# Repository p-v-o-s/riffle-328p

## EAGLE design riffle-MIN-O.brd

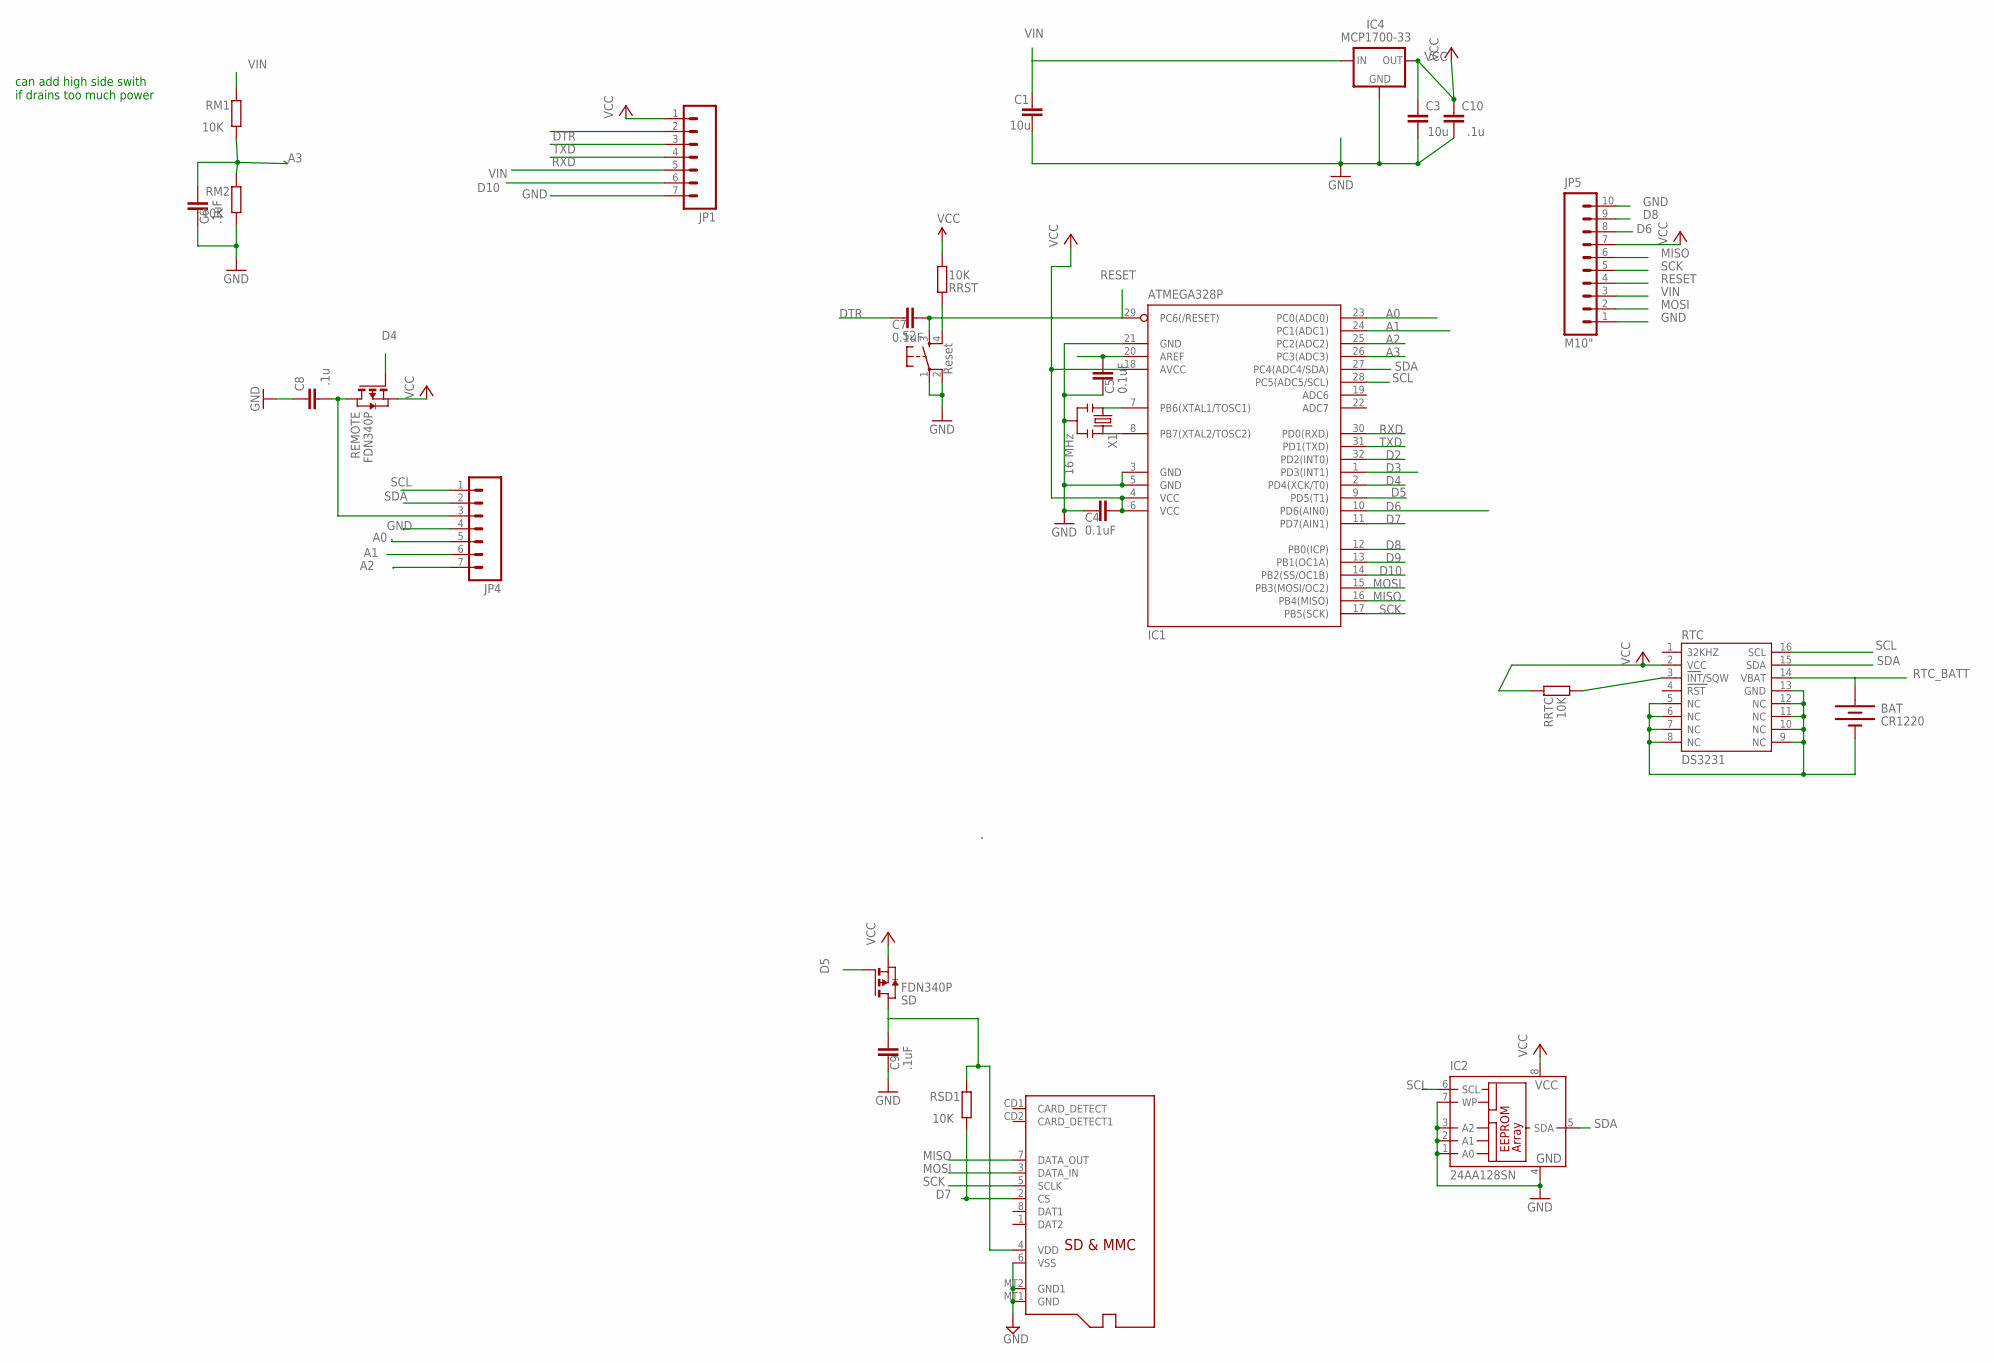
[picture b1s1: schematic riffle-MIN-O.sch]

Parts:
BAT: CR1220; BATTCON_12MM_SMT
C1, C3: 10u; C0805
C4, C5, C7: 0.1uF; C0805@1
C6, C9: .1uF; C0805@1
C8, C10: .1u; C0805
IC1: ATMEGA328P; TQFP32-08
IC2: 24AA128SN; SO-08
IC4: MCP1700-33; SOT23
JP1, JP4: M07; 1X07
JP5: M10"; 1X10
MICROSD: MICROSD
REMOTE: FDN340P; SOT-23
RM1, RM2: 10K; R0805
RRST: 10K; R0805
RRTC: 10K; R0805
RSD1: 10K; R0805
RTC: DS3231
S2: Reset; TACTILE_SWITCH_SMD
SD: FDN340P; SOT-23
X1: 16 MHz; RESONATOR-SMD

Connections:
A0: IC1.23 (PC0(ADC0)), JP4.5
A1: IC1.24 (PC1(ADC1)), JP4.6
A2: IC1.25 (PC2(ADC2)), JP4.7
A3: C6.2, IC1.26 (PC3(ADC3)), RM1.1, RM2.2
AREF: C5.2, IC1.20 (AREF)
D2: IC1.32 (PD2(INT0))
D3: IC1.1 (PD3(INT1))
D4: IC1.2 (PD4(XCK/T0)), REMOTE.3 (G)
D5: IC1.9 (PD5(T1)), SD.3 (G)
D6: IC1.10 (PD6(AIN0)), JP5.8
D7: IC1.11 (PD7(AIN1)), MICROSD.2 (CS), RSD1.1
D8: IC1.12 (PB0(ICP)), JP5.9
D9: IC1.13 (PB1(OC1A))
D10: IC1.14 (PB2(SS/OC1B)), JP1.6
DTR: C7.1, JP1.2
GND: BAT.P$1 (-), C1.2, C3.2, C4.1, C5.1, C6.1, C8.1, C9.1, C10.2, IC1.3 (GND), IC1.5 (GND), IC1.21 (GND), IC2.1 (A0), IC2.2 (A1), IC2.3 (A2), IC2.4 (GND), IC2.7 (WP), IC4.1 (GND), JP1.7, JP4.4, JP5.1, JP5.10, MICROSD.6 (VSS), MICROSD.MT1 (GND), MICROSD.MT2 (GND1), RM2.1, RTC.5 (NC), RTC.6 (NC), RTC.7 (NC), RTC.8 (NC), RTC.9 (NC), RTC.10 (NC), RTC.11 (NC), RTC.12 (NC), RTC.13 (GND), S2.1, S2.2, X1.2
MISO: IC1.16 (PB4(MISO)), JP5.6, MICROSD.7 (DATA_OUT)
MOSI: IC1.15 (PB3(MOSI/OC2)), JP5.2, MICROSD.3 (DATA_IN)
unnamed: IC1.8 (PB7(XTAL2/TOSC2)), X1.3
unnamed: IC1.7 (PB6(XTAL1/TOSC1)), X1.1
unnamed: RRTC.1, RTC.3 (INT/SQW)
RESET: C7.2, IC1.29 (PC6(/RESET)), JP5.4, RRST.2, S2.3, S2.4
RTC_BATT: BAT.P$2 (+), RTC.14 (VBAT)
RXD: IC1.30 (PD0(RXD)), JP1.4
SCK: IC1.17 (PB5(SCK)), JP5.5, MICROSD.5 (SCLK)
SCL: IC1.28 (PC5(ADC5/SCL)), IC2.6 (SCL), JP4.1, RTC.16 (SCL)
SDA: IC1.27 (PC4(ADC4/SDA)), IC2.5 (SDA), JP4.2, RTC.15 (SDA)
TXD: IC1.31 (PD1(TXD)), JP1.3
VCC: C3.1, C4.2, C8.2, C10.1, IC1.4 (VCC), IC1.6 (VCC), IC1.18 (AVCC), IC2.8 (VCC), IC4.2 (OUT), JP1.1, JP4.3, JP5.7, REMOTE.1 (D), REMOTE.2 (S), RRST.1, RRTC.2, RTC.2 (VCC), SD.2 (S)
VDD: C9.2, MICROSD.4 (VDD), RSD1.2, SD.1 (D)
VIN: C1.1, IC4.3 (IN), JP1.5, JP5.3, RM1.2

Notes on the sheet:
can add high side swith if drains too much power

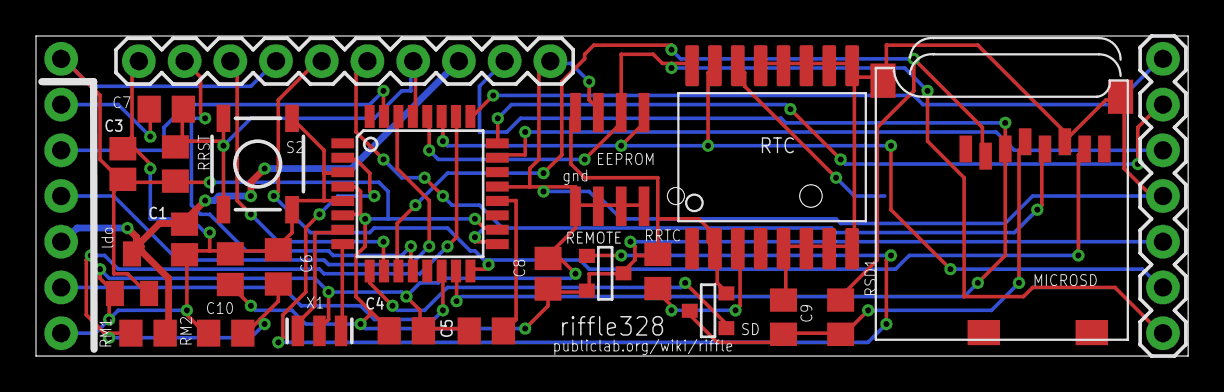
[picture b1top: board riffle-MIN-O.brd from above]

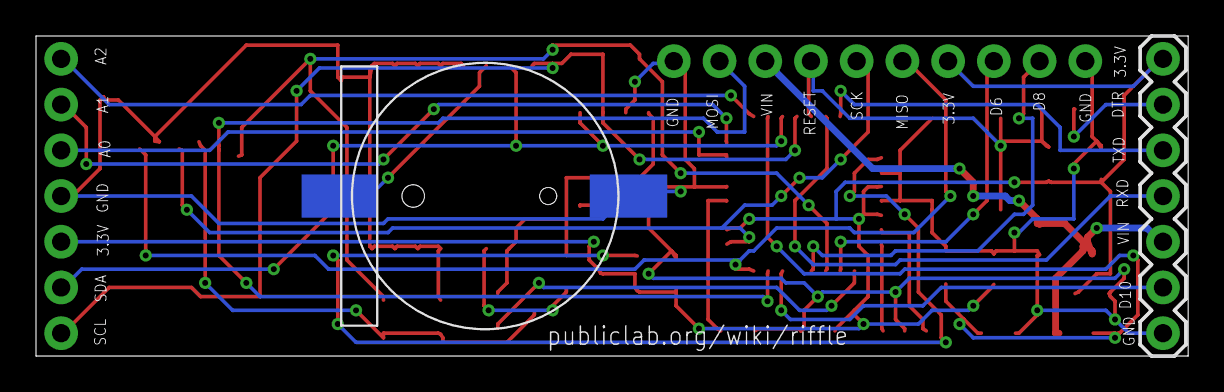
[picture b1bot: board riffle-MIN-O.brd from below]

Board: 2 copper layers, 64.0 x 17.8 mm, 27 parts (2 on the bottom side), 28 nets.

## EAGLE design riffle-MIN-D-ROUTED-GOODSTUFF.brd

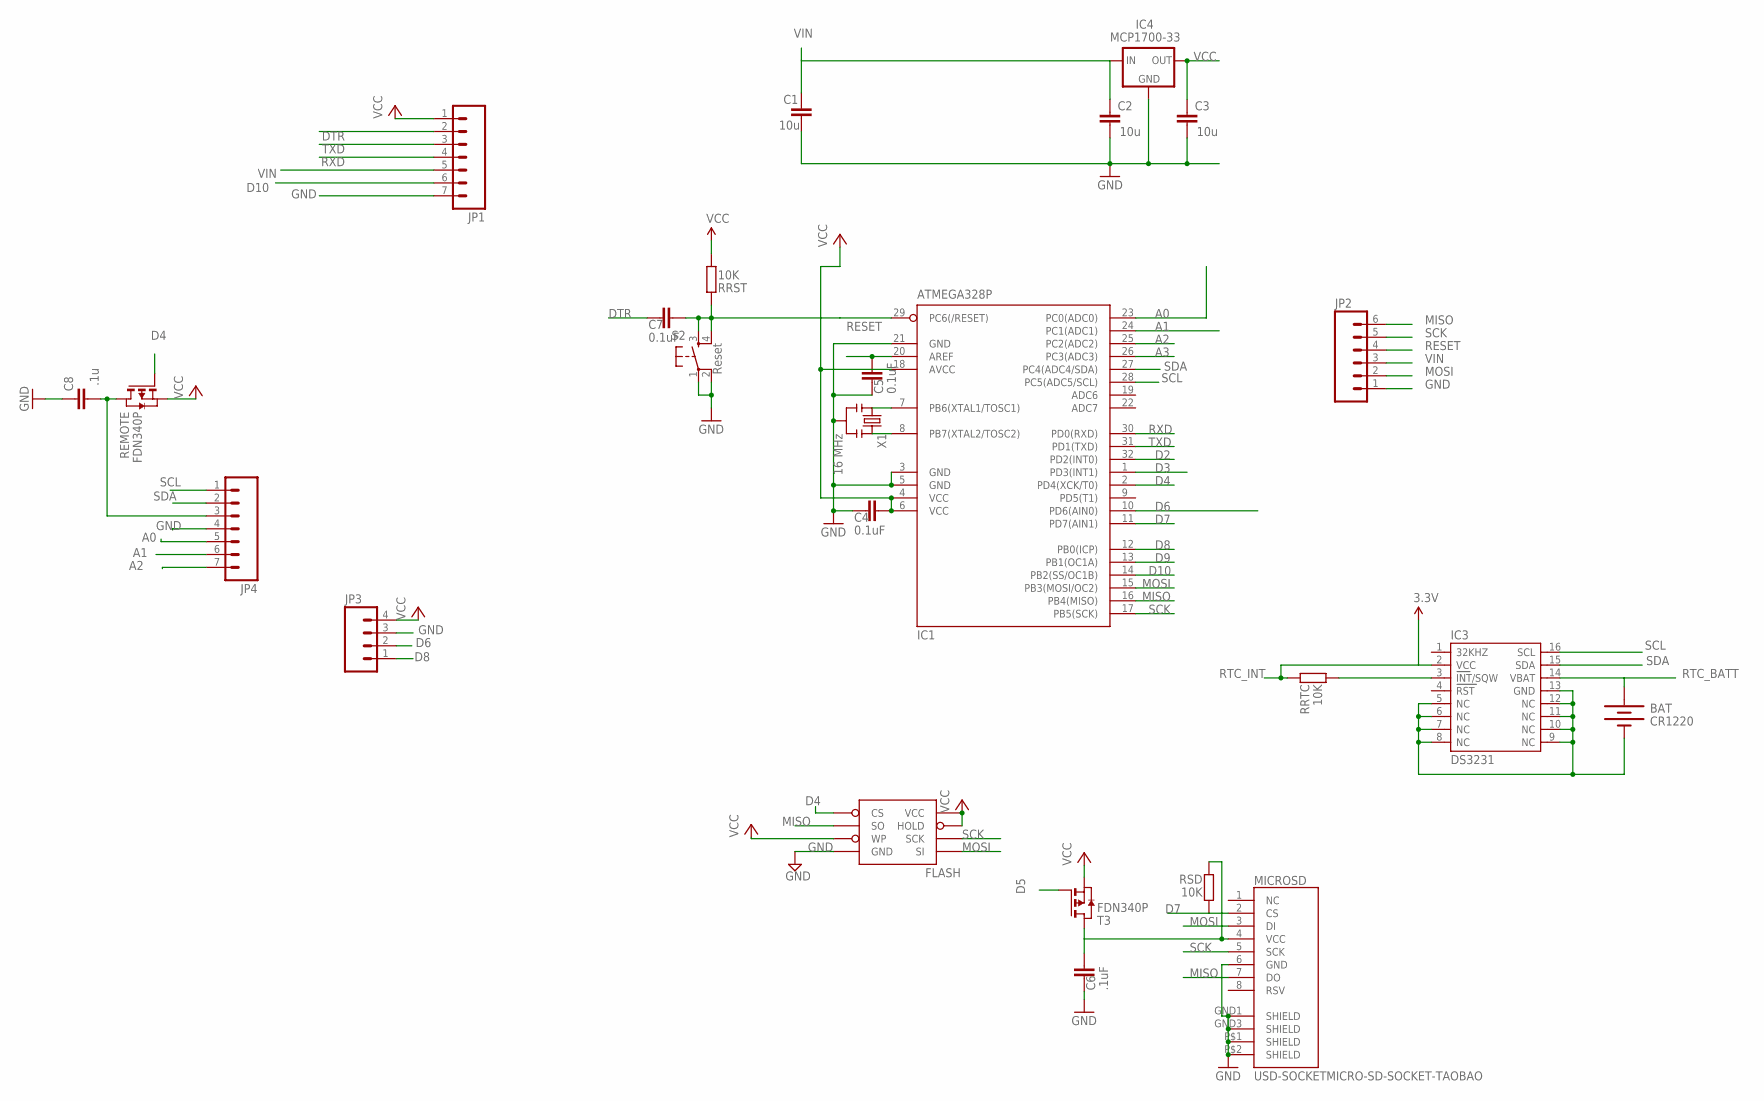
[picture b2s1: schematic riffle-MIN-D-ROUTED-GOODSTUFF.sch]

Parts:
BAT: CR1220; BATTCON_12MM_SMT
C1, C2, C3: 10u; C0805
C4, C5, C7: 0.1uF; C0805@1
C6: .1uF; C0805@1
C8: .1u; C0805
FLASH: AT25F512BWIDE_5.3MM; SO08WIDE
IC1: ATMEGA328P; TQFP32-08
IC3: DS3231
IC4: MCP1700-33; SOT23
JP1, JP4: M07; 1X07
JP2: M06LOCK; 1X06_LOCK
JP3: M04LOCK; 1X04_LOCK
MICROSD: USD-SOCKETMICRO-SD-SOCKET-TAOBAO; MICRO-SD-SOCKET-TAOBAO
REMOTE: FDN340P; SOT-23
RRST: 10K; R0805
RRTC: 10K; R0805
RSD: 10K; R0805
S2: Reset; TACTILE_SWITCH_SMD
T3: FDN340P; SOT-23
X1: 16 MHz; RESONATOR-SMD

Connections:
A0: IC1.23 (PC0(ADC0)), JP4.5
A1: IC1.24 (PC1(ADC1)), JP4.6
A2: IC1.25 (PC2(ADC2)), JP4.7
A3: IC1.26 (PC3(ADC3))
AREF: C5.2, IC1.20 (AREF)
D2: IC1.32 (PD2(INT0))
D3: IC1.1 (PD3(INT1))
D4: FLASH.1 (CS), IC1.2 (PD4(XCK/T0)), REMOTE.3 (G)
D5: T3.3 (G)
D6: IC1.10 (PD6(AIN0)), JP3.2
D7: IC1.11 (PD7(AIN1)), MICROSD.2 (CS), RSD.1
D8: IC1.12 (PB0(ICP)), JP3.1
D9: IC1.13 (PB1(OC1A))
D10: IC1.14 (PB2(SS/OC1B)), JP1.6
DTR: C7.1, JP1.2
GND: BAT.P$1 (-), C1.2, C2.2, C3.2, C4.1, C5.1, C6.1, C8.1, FLASH.4 (GND), IC1.3 (GND), IC1.5 (GND), IC1.21 (GND), IC3.5 (NC), IC3.6 (NC), IC3.7 (NC), IC3.8 (NC), IC3.9 (NC), IC3.10 (NC), IC3.11 (NC), IC3.12 (NC), IC3.13 (GND), IC4.1 (GND), JP1.7, JP2.1, JP3.3, JP4.4, MICROSD.6 (GND), MICROSD.GND1 (SHIELD), MICROSD.GND3 (SHIELD), MICROSD.P$1 (SHIELD), MICROSD.P$2 (SHIELD), S2.1, S2.2, X1.2
MISO: FLASH.2 (SO), IC1.16 (PB4(MISO)), JP2.6, MICROSD.7 (DO)
MOSI: FLASH.5 (SI), IC1.15 (PB3(MOSI/OC2)), JP2.2, MICROSD.3 (DI)
unnamed: IC1.8 (PB7(XTAL2/TOSC2)), X1.3
unnamed: IC1.7 (PB6(XTAL1/TOSC1)), X1.1
unnamed: IC3.3 (INT/SQW), RRTC.1
unnamed: C6.2, MICROSD.4 (VCC), RSD.2, T3.1 (D)
RESET: IC1.29 (PC6(/RESET)), JP2.4
RESET1: C7.2, RRST.2, S2.3, S2.4
RTC_BATT: BAT.P$2 (+), IC3.14 (VBAT)
RTC_INT: IC3.2 (VCC), RRTC.2
RXD: IC1.30 (PD0(RXD)), JP1.4
SCK: FLASH.6 (SCK), IC1.17 (PB5(SCK)), JP2.5, MICROSD.5 (SCK)
SCL: IC1.28 (PC5(ADC5/SCL)), IC3.16 (SCL), JP4.1
SDA: IC1.27 (PC4(ADC4/SDA)), IC3.15 (SDA), JP4.2
TXD: IC1.31 (PD1(TXD)), JP1.3
VCC: C3.1, C4.2, C8.2, FLASH.3 (WP), FLASH.7 (HOLD), FLASH.8 (VCC), IC1.4 (VCC), IC1.6 (VCC), IC1.18 (AVCC), IC4.2 (OUT), JP1.1, JP3.4, JP4.3, REMOTE.1 (D), REMOTE.2 (S), RRST.1, T3.2 (S)
VIN: C1.1, C2.1, IC4.3 (IN), JP1.5, JP2.3

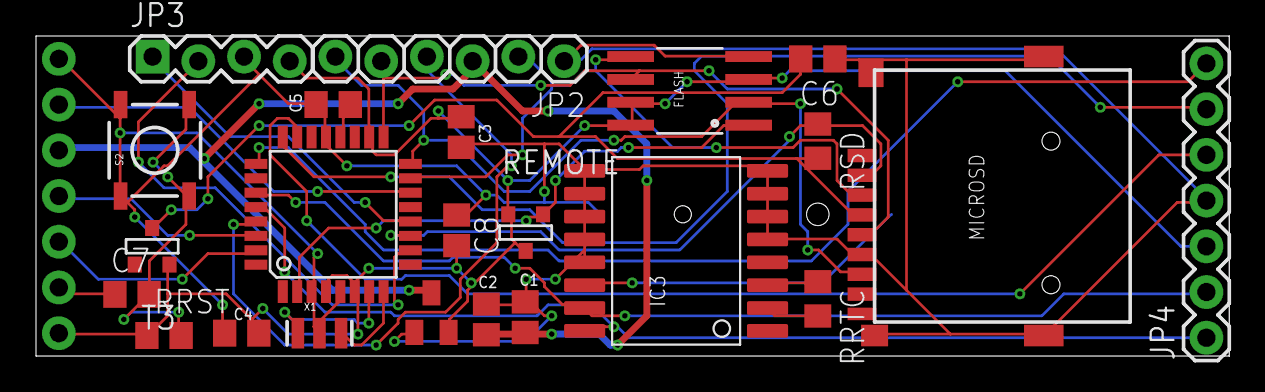
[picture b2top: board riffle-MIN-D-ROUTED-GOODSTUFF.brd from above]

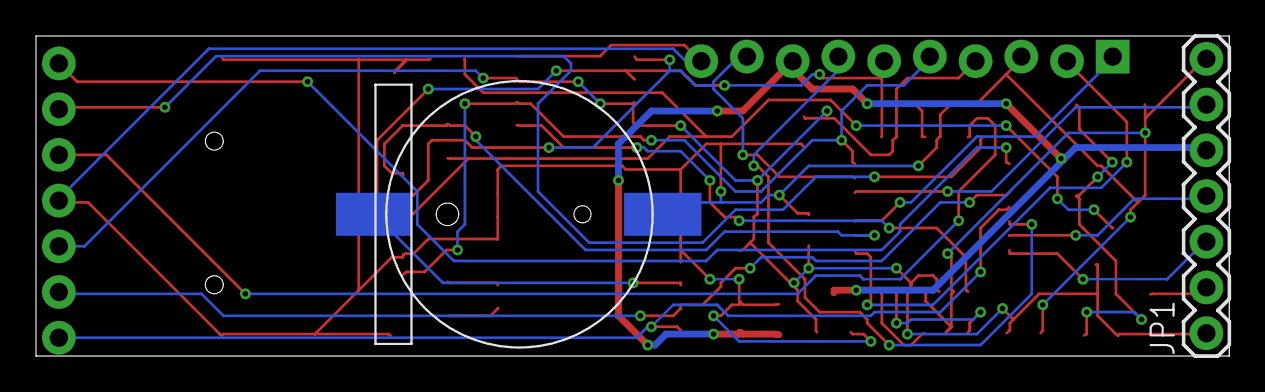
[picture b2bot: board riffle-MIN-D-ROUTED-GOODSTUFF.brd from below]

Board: 2 copper layers, 66.3 x 17.8 mm, 25 parts (2 on the bottom side), 28 nets.

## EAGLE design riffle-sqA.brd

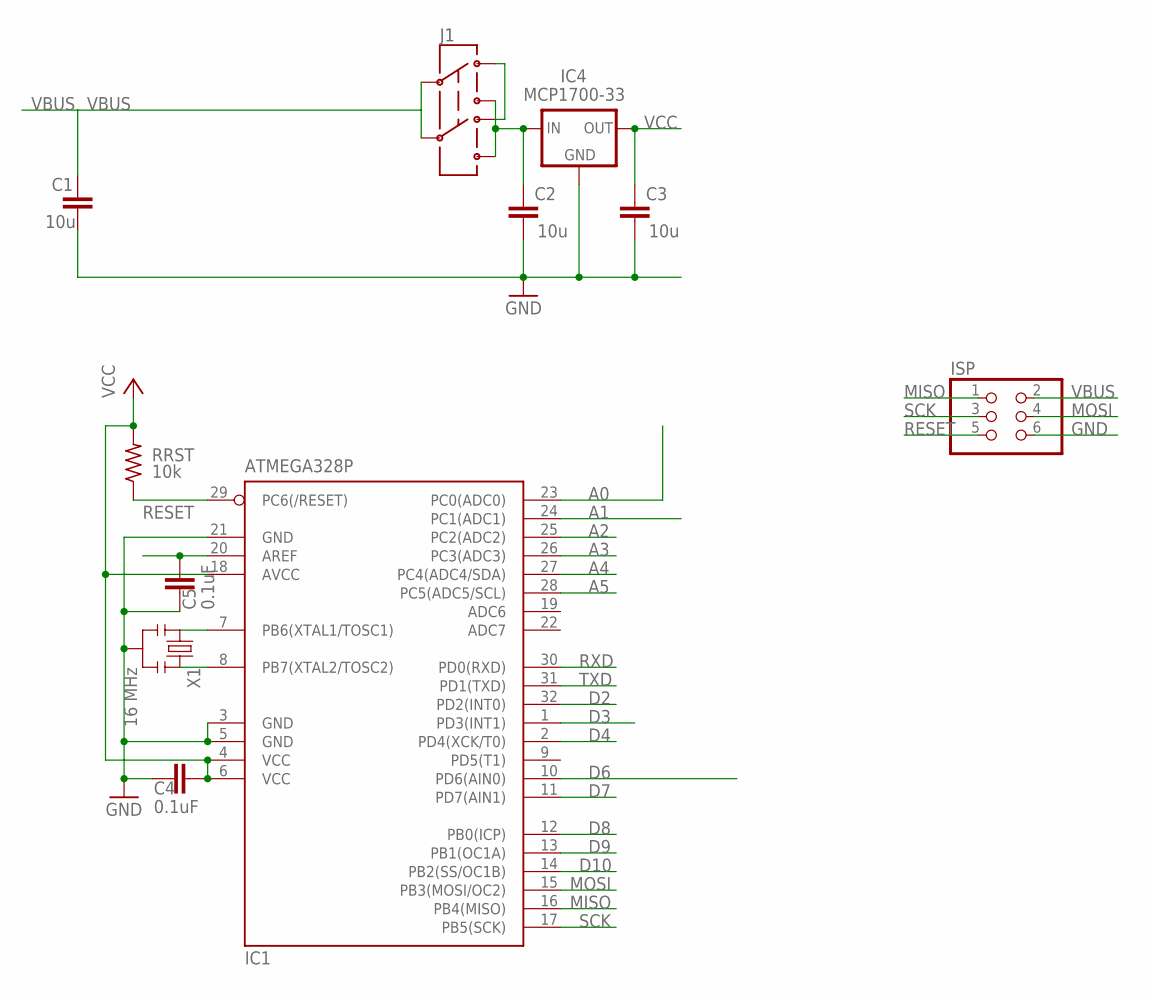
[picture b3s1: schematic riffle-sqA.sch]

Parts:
C1, C2, C3: 10u; C0805
C4, C5: 0.1uF; C0805
IC1: ATMEGA328P; TQFP32-08
IC4: MCP1700-33; SOT23
ISP: PINHD-2X3; 2X03
J1: AYZ0202
RRST: 10k; R0805@1
X1: 16 MHz; RESONATOR-SMD

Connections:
A0: IC1.23 (PC0(ADC0))
A1: IC1.24 (PC1(ADC1))
A2: IC1.25 (PC2(ADC2))
A3: IC1.26 (PC3(ADC3))
A4: IC1.27 (PC4(ADC4/SDA))
A5: IC1.28 (PC5(ADC5/SCL))
AREF: C5.2, IC1.20 (AREF)
D2: IC1.32 (PD2(INT0))
D3: IC1.1 (PD3(INT1))
D4: IC1.2 (PD4(XCK/T0))
D6: IC1.10 (PD6(AIN0))
D7: IC1.11 (PD7(AIN1))
D8: IC1.12 (PB0(ICP))
D9: IC1.13 (PB1(OC1A))
D10: IC1.14 (PB2(SS/OC1B))
GND: C1.2, C2.2, C3.2, C4.1, C5.1, IC1.3 (GND), IC1.5 (GND), IC1.21 (GND), IC4.1 (GND), ISP.6, X1.2
MISO: IC1.16 (PB4(MISO)), ISP.1
MOSI: IC1.15 (PB3(MOSI/OC2)), ISP.4
unnamed: J1.3 (1), J1.6 (4)
unnamed: IC1.8 (PB7(XTAL2/TOSC2)), X1.3
unnamed: IC1.7 (PB6(XTAL1/TOSC1)), X1.1
RESET: IC1.29 (PC6(/RESET)), ISP.5, RRST.1
RXD: IC1.30 (PD0(RXD))
SCK: IC1.17 (PB5(SCK)), ISP.3
TXD: IC1.31 (PD1(TXD))
VBUS: C1.1, ISP.2, J1.2, J1.5
VCC: C3.1, C4.2, IC1.4 (VCC), IC1.6 (VCC), IC1.18 (AVCC), IC4.2 (OUT), RRST.2
VDD: C2.1, IC4.3 (IN), J1.1 (3), J1.4 (6)

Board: 2 copper layers, 11 parts (1 on the bottom side), 12 nets, no tracks yet.

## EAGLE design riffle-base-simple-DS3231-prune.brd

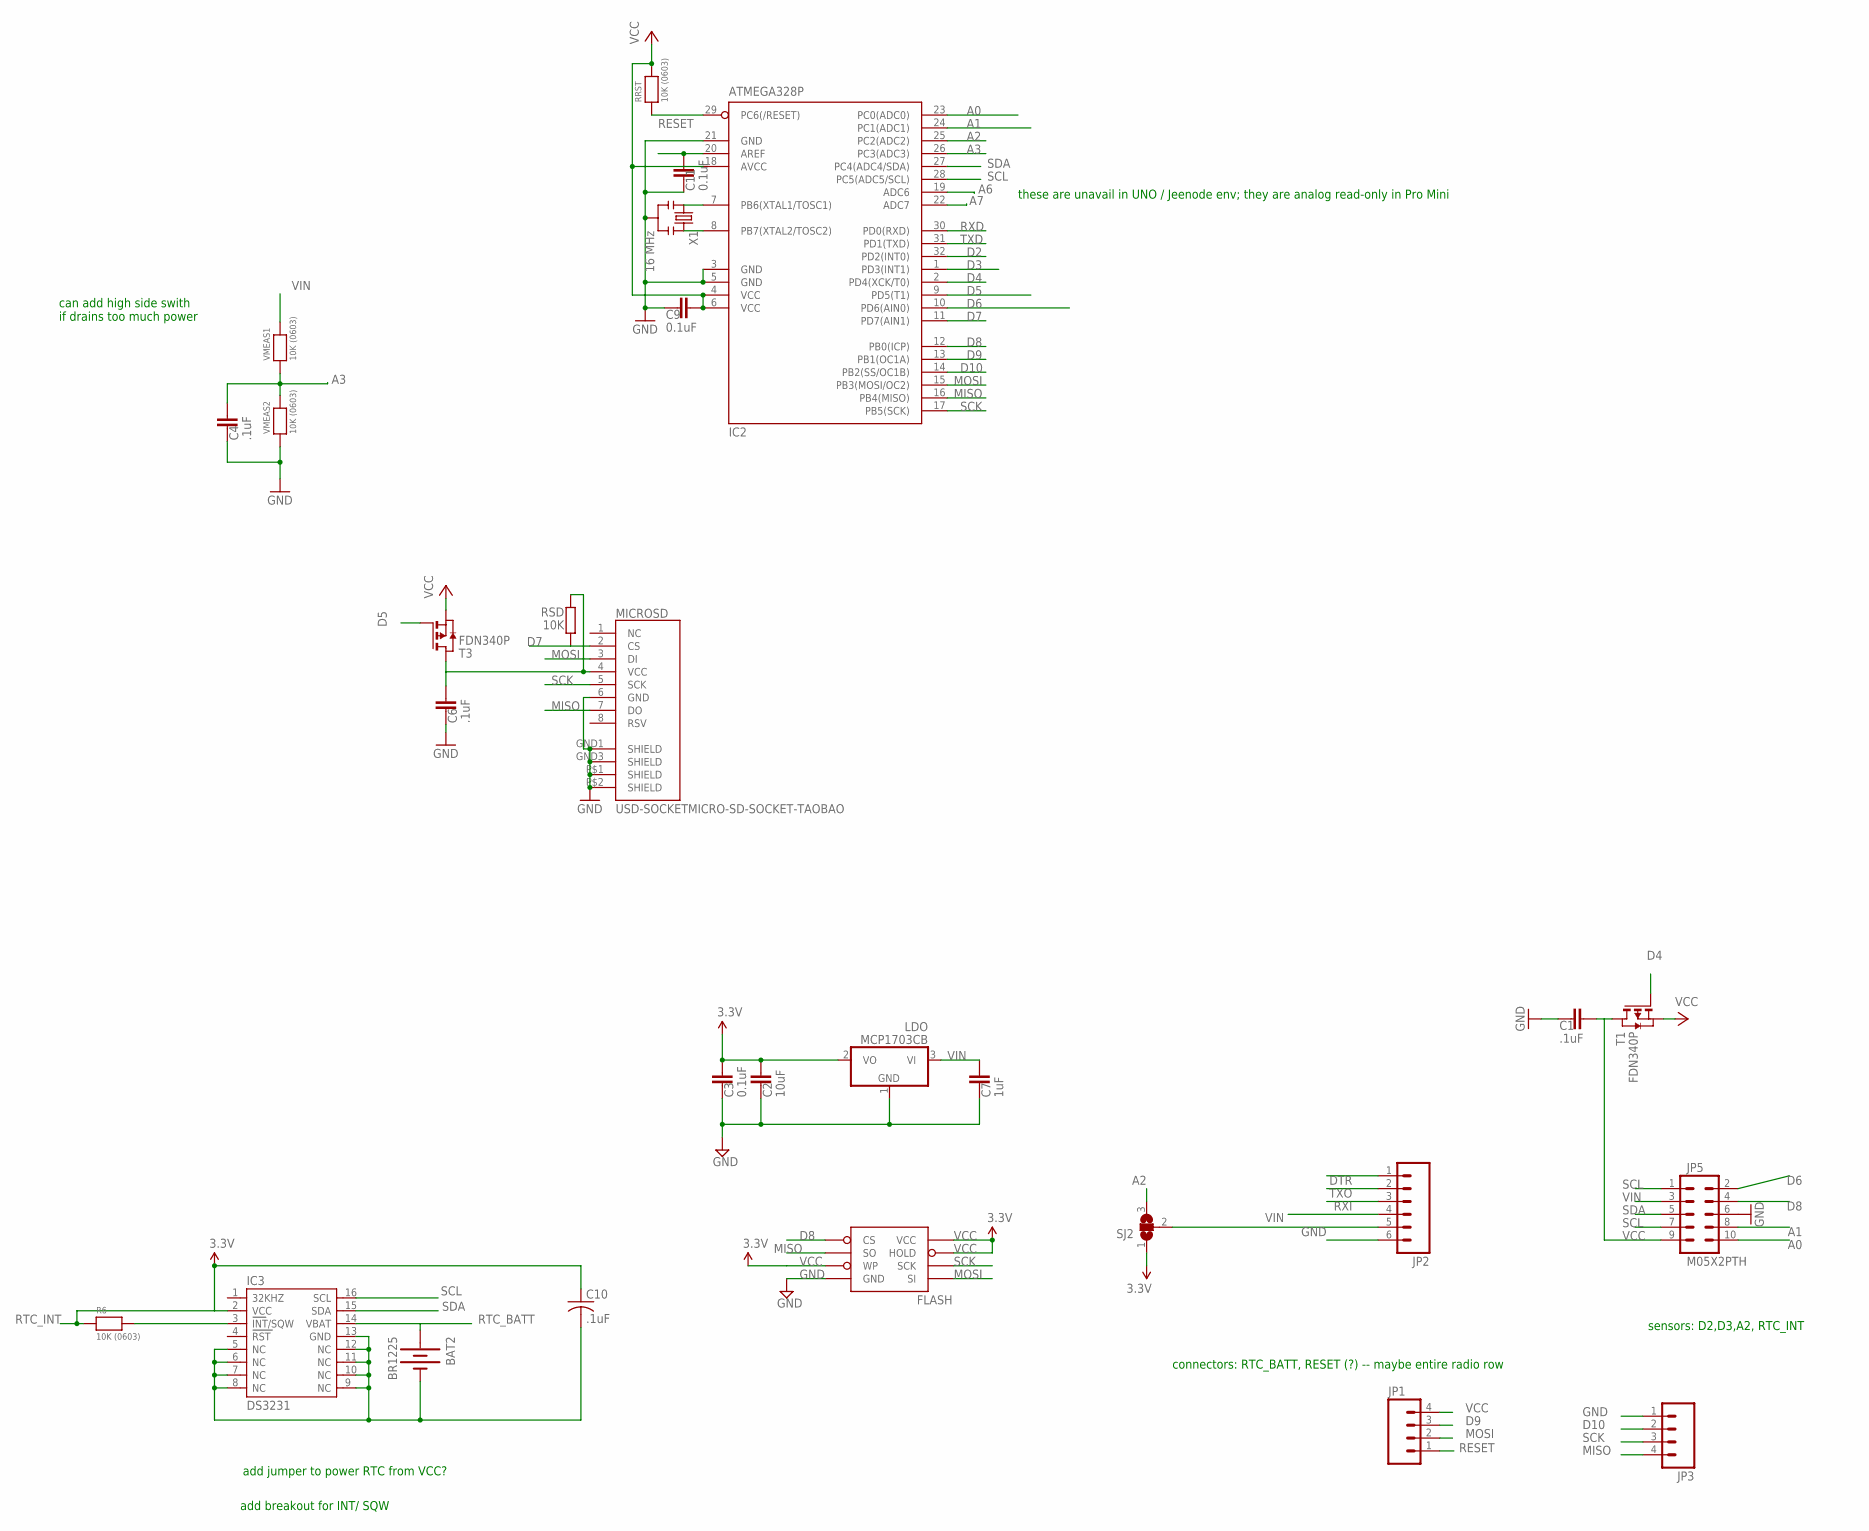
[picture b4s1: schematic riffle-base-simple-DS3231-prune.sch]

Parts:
BAT2: BR1225; BATTCON_12MM_PTH
C1, C4, C6: .1uF; C0805@1
C2: 10uF; C0805@1
C3, C9, C11: 0.1uF; C0805@1
C7: 1uF; C0805@1
C10: .1uF; C0805
FLASH: AT25F512BWIDE_5.3MM; SO08WIDE
IC2: ATMEGA328P; TQFP32-08
IC3: DS3231
JP1, JP3: M04LOCK; 1X04_LOCK
JP2: M06LOCK; 1X06_LOCK
JP5: M05X2PTH; AVR_ICSP
LDO: MCP1703CB; SOT23
MICROSD: USD-SOCKETMICRO-SD-SOCKET-TAOBAO; MICRO-SD-SOCKET-TAOBAO
R6: 10K (0603); 0603-NO
RRST: 10K (0603); 0603-NO
RSD: 10K; R0805
SJ2: SJ2W; SJ_2
T1, T3: FDN340P; SOT-23
VMEAS1, VMEAS2: 10K (0603); 0603-NO
X1: 16 MHz; RESONATOR-SMD

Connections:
A0: IC2.23 (PC0(ADC0)), JP5.10
A1: IC2.24 (PC1(ADC1)), JP5.8
A2: IC2.25 (PC2(ADC2)), SJ2.3
A3: C4.2, IC2.26 (PC3(ADC3)), VMEAS1.1, VMEAS2.2
A6: IC2.19 (ADC6)
A7: IC2.22 (ADC7)
AREF: C11.2, IC2.20 (AREF)
D2: IC2.32 (PD2(INT0))
D3: IC2.1 (PD3(INT1))
D4: IC2.2 (PD4(XCK/T0)), T1.3 (G)
D5: IC2.9 (PD5(T1)), T3.3 (G)
D6: IC2.10 (PD6(AIN0)), JP5.2
D7: IC2.11 (PD7(AIN1)), MICROSD.2 (CS), RSD.1
D8: FLASH.1 (CS), IC2.12 (PB0(ICP)), JP5.4
D9: IC2.13 (PB1(OC1A)), JP1.3
D10: IC2.14 (PB2(SS/OC1B)), JP3.2
DTR: JP2.1
GND: BAT2.GND (-), C1.1, C2.1, C3.1, C4.1, C6.1, C7.1, C9.1, C10.2, C11.1, FLASH.4 (GND), IC2.3 (GND), IC2.5 (GND), IC2.21 (GND), IC3.5 (NC), IC3.6 (NC), IC3.7 (NC), IC3.8 (NC), IC3.9 (NC), IC3.10 (NC), IC3.11 (NC), IC3.12 (NC), IC3.13 (GND), JP2.6, JP3.1, JP5.6, LDO.1 (GND), MICROSD.6 (GND), MICROSD.GND1 (SHIELD), MICROSD.GND3 (SHIELD), MICROSD.P$1 (SHIELD), MICROSD.P$2 (SHIELD), VMEAS2.1, X1.2
MISO: FLASH.2 (SO), IC2.16 (PB4(MISO)), JP3.4, MICROSD.7 (DO)
MOSI: FLASH.5 (SI), IC2.15 (PB3(MOSI/OC2)), JP1.2, MICROSD.3 (DI)
unnamed: IC2.8 (PB7(XTAL2/TOSC2)), X1.3
unnamed: JP2.5, SJ2.2
unnamed: IC2.7 (PB6(XTAL1/TOSC1)), X1.1
unnamed: IC3.3 (INT/SQW), R6.2
unnamed: C6.2, MICROSD.4 (VCC), RSD.2, T3.1 (D)
RESET: IC2.29 (PC6(/RESET)), JP1.1, RRST.1
RTC_BATT: BAT2.VCC@1 (+), IC3.14 (VBAT)
RTC_INT: C10.1, IC3.2 (VCC), R6.1
RXD: IC2.30 (PD0(RXD))
RXI: JP2.3
SCK: FLASH.6 (SCK), IC2.17 (PB5(SCK)), JP3.3, MICROSD.5 (SCK)
SCL: IC2.28 (PC5(ADC5/SCL)), IC3.16 (SCL), JP5.1, JP5.7
SDA: IC2.27 (PC4(ADC4/SDA)), IC3.15 (SDA), JP5.5
TXD: IC2.31 (PD1(TXD))
TXO: JP2.2
VCC: C1.2, C2.2, C3.2, C9.2, FLASH.3 (WP), FLASH.7 (HOLD), FLASH.8 (VCC), IC2.4 (VCC), IC2.6 (VCC), IC2.18 (AVCC), JP1.4, JP5.9, LDO.2 (VO), RRST.2, SJ2.1, T1.1 (D), T1.2 (S), T3.2 (S)
VIN: C7.2, JP2.4, JP5.3, LDO.3 (VI), VMEAS1.2

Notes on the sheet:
these are unavail in UNO / Jeenode env; they are analog read-only in Pro Mini
can add high side swith if drains too much power
add jumper to power RTC from VCC?
add breakout for INT/ SQW
sensors: D2,D3,A2, RTC_INT
connectors: RTC_BATT, RESET (?) -- maybe entire radio row

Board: 2 copper layers, 28 parts (2 on the bottom side), 28 nets, no tracks yet.

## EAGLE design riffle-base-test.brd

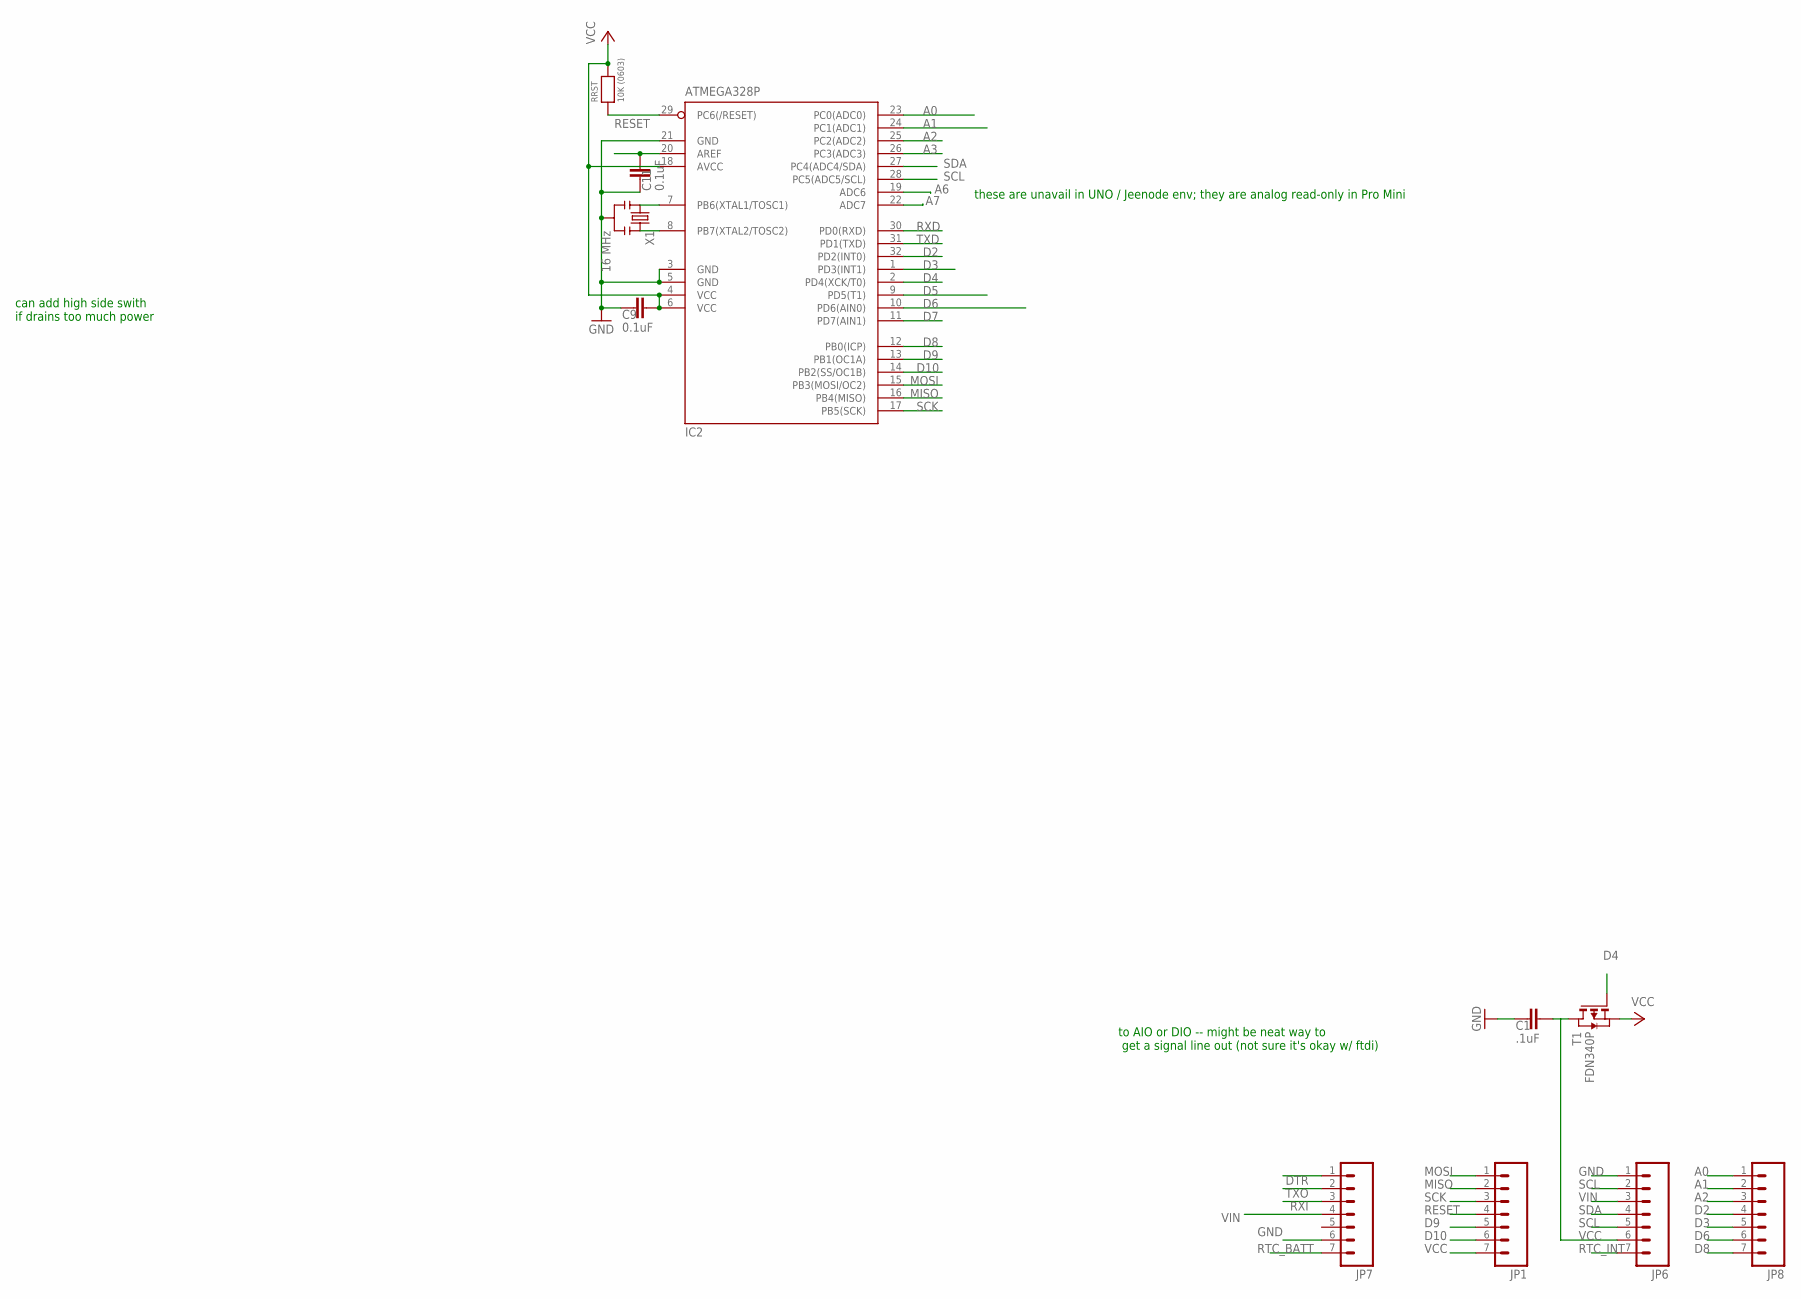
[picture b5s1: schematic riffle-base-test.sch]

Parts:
C1: .1uF; C0805@1
C9, C11: 0.1uF; C0805@1
IC2: ATMEGA328P; TQFP32-08
JP1, JP6, JP7, JP8: M07; 1X07
RRST: 10K (0603); 0603-NO
T1: FDN340P; SOT-23
X1: 16 MHz; RESONATOR-SMD

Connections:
A0: IC2.23 (PC0(ADC0)), JP8.1
A1: IC2.24 (PC1(ADC1)), JP8.2
A2: IC2.25 (PC2(ADC2)), JP8.3
A3: IC2.26 (PC3(ADC3))
A6: IC2.19 (ADC6)
A7: IC2.22 (ADC7)
AREF: C11.2, IC2.20 (AREF)
D2: IC2.32 (PD2(INT0)), JP8.4
D3: IC2.1 (PD3(INT1)), JP8.5
D4: IC2.2 (PD4(XCK/T0)), T1.3 (G)
D5: IC2.9 (PD5(T1))
D6: IC2.10 (PD6(AIN0)), JP8.6
D7: IC2.11 (PD7(AIN1))
D8: IC2.12 (PB0(ICP)), JP8.7
D9: IC2.13 (PB1(OC1A)), JP1.5
D10: IC2.14 (PB2(SS/OC1B)), JP1.6
DTR: JP7.1
GND: C1.1, C9.1, C11.1, IC2.3 (GND), IC2.5 (GND), IC2.21 (GND), JP6.1, JP7.6, X1.2
MISO: IC2.16 (PB4(MISO)), JP1.2
MOSI: IC2.15 (PB3(MOSI/OC2)), JP1.1
unnamed: IC2.8 (PB7(XTAL2/TOSC2)), X1.3
unnamed: IC2.7 (PB6(XTAL1/TOSC1)), X1.1
RESET: IC2.29 (PC6(/RESET)), JP1.4, RRST.1
RTC_BATT: JP7.7
RTC_INT: JP6.7
RXD: IC2.30 (PD0(RXD))
RXI: JP7.3
SCK: IC2.17 (PB5(SCK)), JP1.3
SCL: IC2.28 (PC5(ADC5/SCL)), JP6.2, JP6.5
SDA: IC2.27 (PC4(ADC4/SDA)), JP6.4
TXD: IC2.31 (PD1(TXD))
TXO: JP7.2
VCC: C1.2, C9.2, IC2.4 (VCC), IC2.6 (VCC), IC2.18 (AVCC), JP1.7, JP6.6, RRST.2, T1.1 (D), T1.2 (S)
VIN: JP6.3, JP7.4

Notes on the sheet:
to AIO or DIO -- might be neat way to get a signal line out (not sure it's okay w/ ftdi)
these are unavail in UNO / Jeenode env; they are analog read-only in Pro Mini
can add high side swith if drains too much power

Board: 2 copper layers, 11 parts (0 on the bottom side), 22 nets, no tracks yet.

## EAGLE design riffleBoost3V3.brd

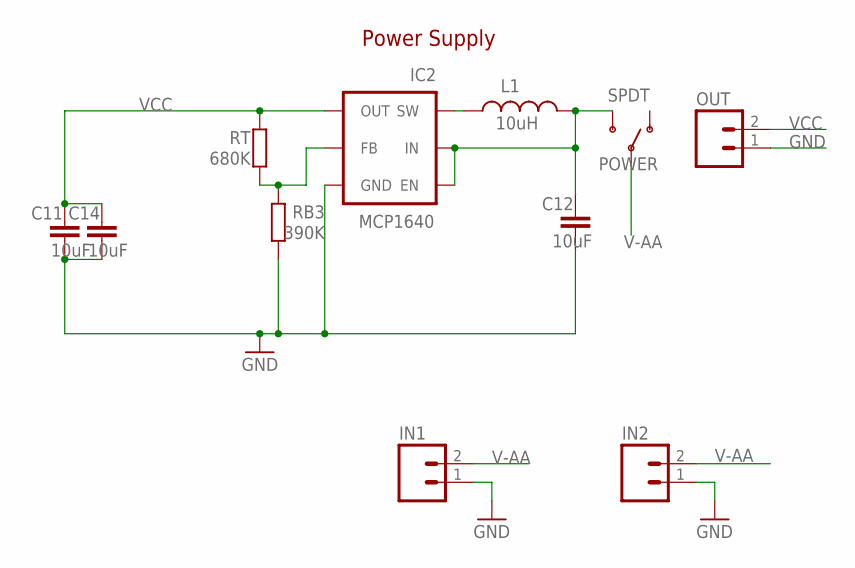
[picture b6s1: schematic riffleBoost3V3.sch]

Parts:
C11, C12, C14: 10uF; C0805
IC2: MCP1640; TSOT23-6
IN1: M02PTH; 1X02
IN2: M02-JST-2MM-SMT; JST-2-SMD
L1: 10uH; INDUCTOR_D30
OUT: M021X02_NO_SILK; 1X02_NO_SILK
POWER: SPDT; SWITCH-SPDT-SMD
RB3: 390K; R0805
RT: 680K; R0805

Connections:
GND: C11.2, C12.2, C14.2, IC2.2 (GND), IN1.1, IN2.1, OUT.1, RB3.1
unnamed: IC2.4 (FB), RB3.2, RT.1
unnamed: IC2.1 (SW), L1.P$2 (2)
PWR: C12.1, IC2.3 (EN), IC2.6 (IN), L1.P$1 (1), POWER.3 (S)
V-AA: IN1.2, IN2.2, POWER.2
VCC: C11.1, C14.1, IC2.5 (OUT), OUT.2, RT.2

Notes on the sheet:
Power Supply

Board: 2 copper layers, 11 parts (0 on the bottom side), 6 nets, no tracks yet.

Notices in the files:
parts and their libraries:
SparkFun-Connectors: Licensing: Creative Commons ShareAlike 4.0 International - https://creativecommons.org/licenses/by-sa/4.0
microbuilder: This work is placed in the public domain, and may be freely used for commercial and non-commercial work with the following conditions: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
